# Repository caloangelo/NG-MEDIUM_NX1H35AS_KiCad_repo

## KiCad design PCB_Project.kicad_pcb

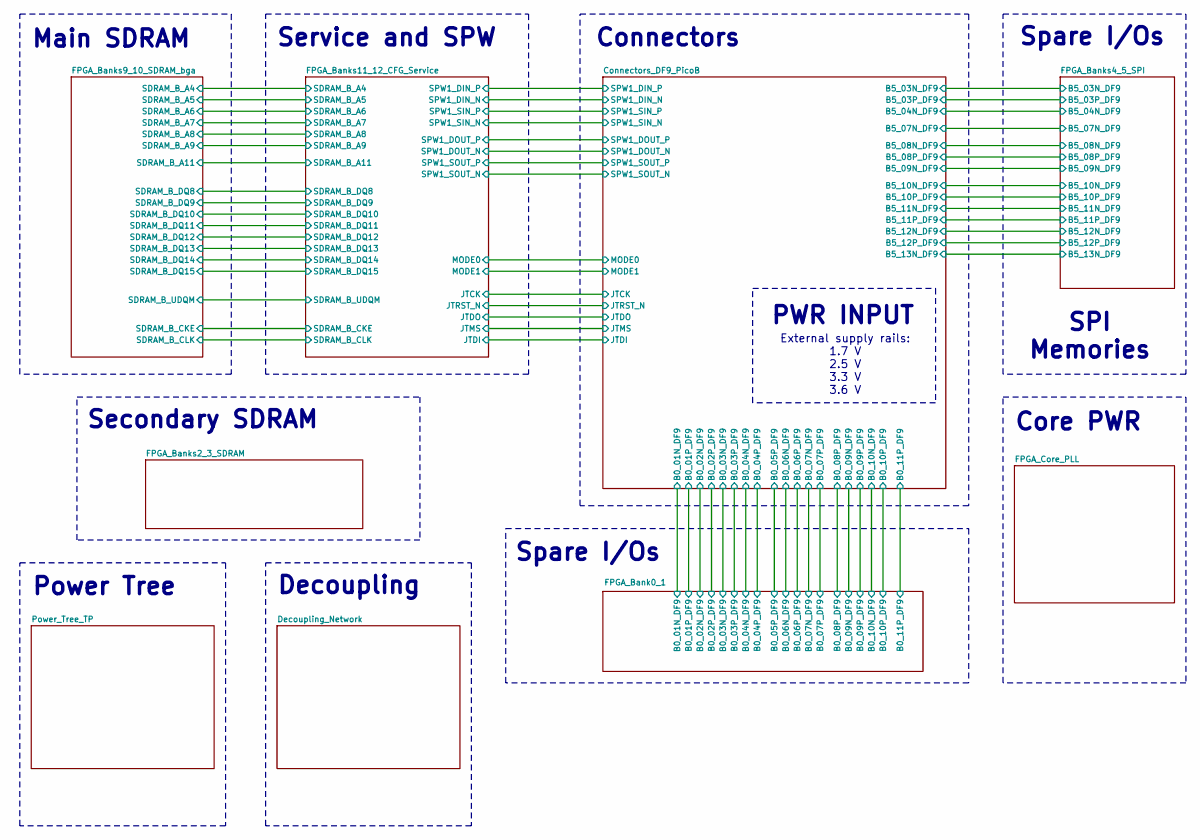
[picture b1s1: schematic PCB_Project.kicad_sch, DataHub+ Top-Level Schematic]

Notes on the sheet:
Spare I/Os
SPI Memories
Secondary SDRAM
Power Tree
Main SDRAM
Service and SPW
PWR INPUT
Decoupling
External supply rails: 1.7 V 2.5 V 3.3 V 3.6 V
Core PWR
Connectors

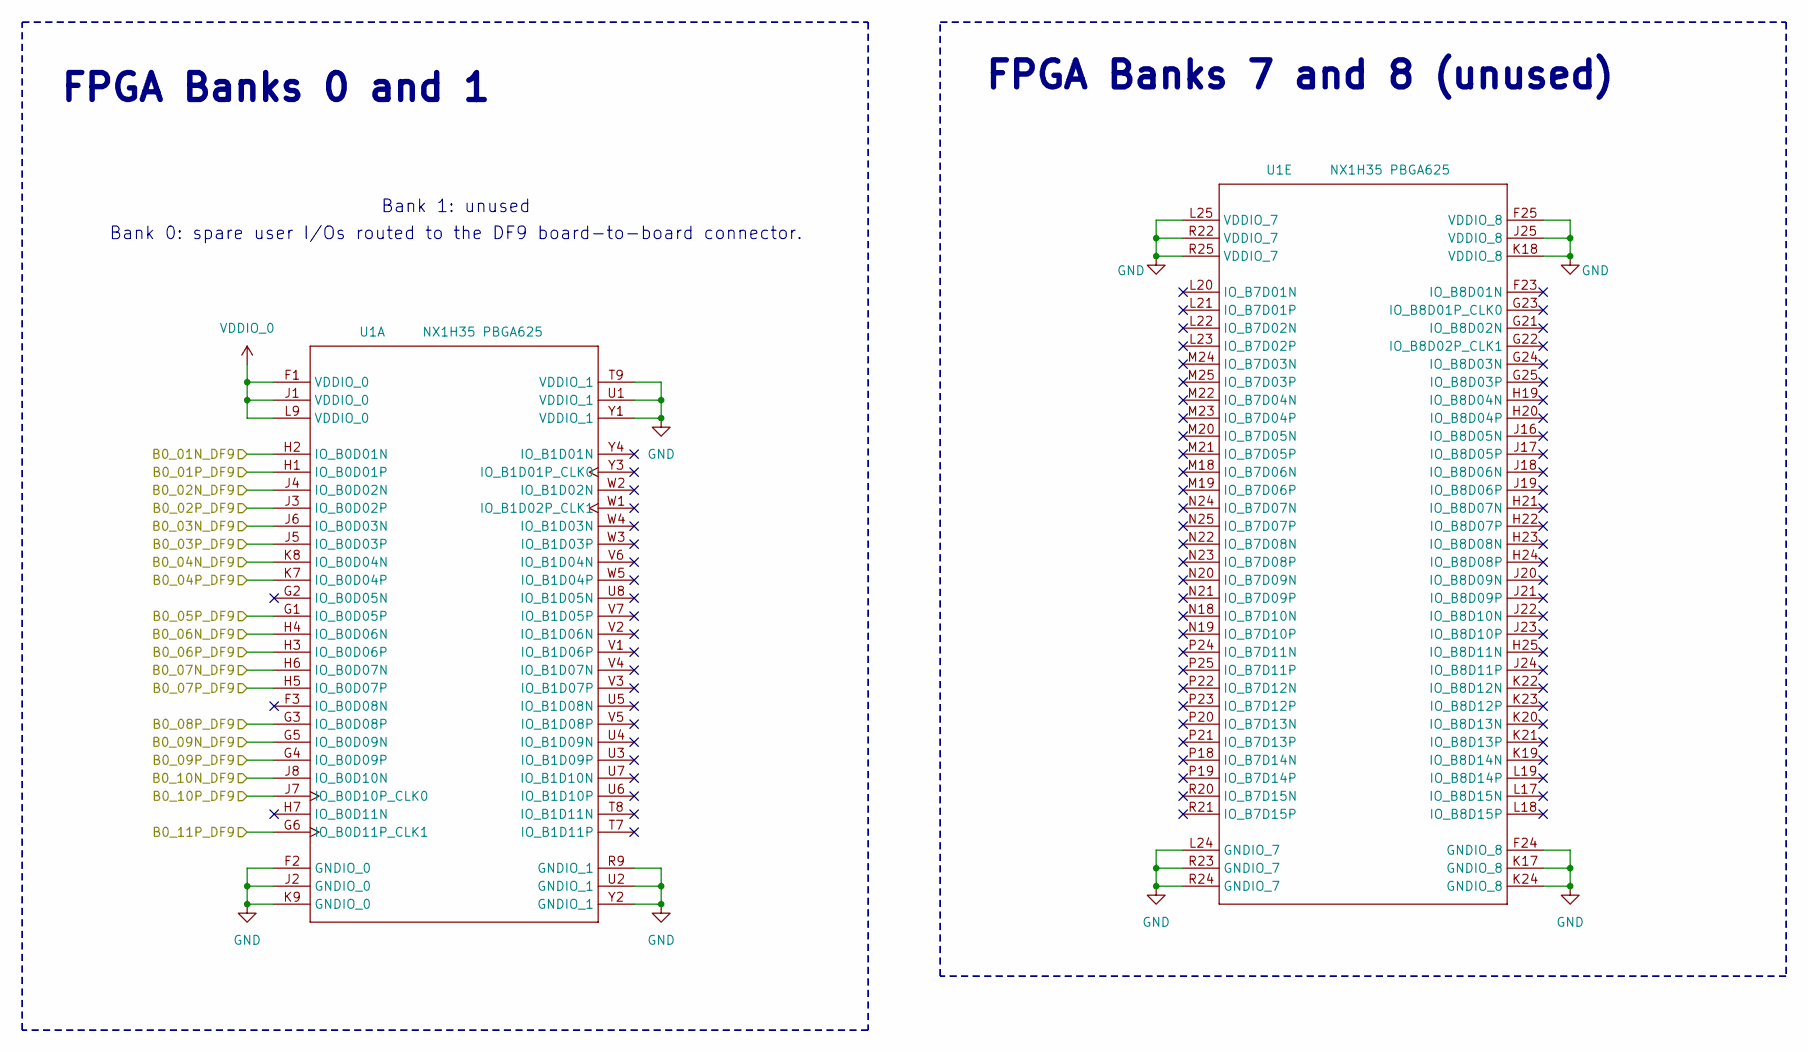
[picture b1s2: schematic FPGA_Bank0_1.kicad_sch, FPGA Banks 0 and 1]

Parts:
U1: NX1H35 PBGA625; NX1H35S_CLGA625

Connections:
/Connectors_DF9_PicoB/B0_01N_DF9: U1.H2 (IO_B0D01N); also elsewhere on the board
/Connectors_DF9_PicoB/B0_01P_DF9: U1.H1 (IO_B0D01P); also elsewhere on the board
/Connectors_DF9_PicoB/B0_02N_DF9: U1.J4 (IO_B0D02N); also elsewhere on the board
/Connectors_DF9_PicoB/B0_02P_DF9: U1.J3 (IO_B0D02P); also elsewhere on the board
/Connectors_DF9_PicoB/B0_03N_DF9: U1.J6 (IO_B0D03N); also elsewhere on the board
/Connectors_DF9_PicoB/B0_03P_DF9: U1.J5 (IO_B0D03P); also elsewhere on the board
/Connectors_DF9_PicoB/B0_04N_DF9: U1.K8 (IO_B0D04N); also elsewhere on the board
/Connectors_DF9_PicoB/B0_04P_DF9: U1.K7 (IO_B0D04P); also elsewhere on the board
/Connectors_DF9_PicoB/B0_05P_DF9: U1.G1 (IO_B0D05P); also elsewhere on the board
/Connectors_DF9_PicoB/B0_06N_DF9: U1.H4 (IO_B0D06N); also elsewhere on the board
/Connectors_DF9_PicoB/B0_06P_DF9: U1.H3 (IO_B0D06P); also elsewhere on the board
/Connectors_DF9_PicoB/B0_07N_DF9: U1.H6 (IO_B0D07N); also elsewhere on the board
/Connectors_DF9_PicoB/B0_07P_DF9: U1.H5 (IO_B0D07P); also elsewhere on the board
/Connectors_DF9_PicoB/B0_08P_DF9: U1.G3 (IO_B0D08P); also elsewhere on the board
/Connectors_DF9_PicoB/B0_09N_DF9: U1.G5 (IO_B0D09N); also elsewhere on the board
/Connectors_DF9_PicoB/B0_09P_DF9: U1.G4 (IO_B0D09P); also elsewhere on the board
/Connectors_DF9_PicoB/B0_10N_DF9: U1.J8 (IO_B0D10N); also elsewhere on the board
/Connectors_DF9_PicoB/B0_10P_DF9: U1.J7 (IO_B0D10P_CLK0); also elsewhere on the board
/Connectors_DF9_PicoB/B0_11P_DF9: U1.G6 (IO_B0D11P_CLK1); also elsewhere on the board
GND: U1.F2 (GNDIO_0), U1.F24 (GNDIO_8), U1.F25 (VDDIO_8), U1.J2 (GNDIO_0), U1.J25 (VDDIO_8), U1.K9 (GNDIO_0), U1.K17 (GNDIO_8), U1.K18 (VDDIO_8), U1.K24 (GNDIO_8), U1.L24 (GNDIO_7), U1.L25 (VDDIO_7), U1.R9 (GNDIO_1), U1.R22 (VDDIO_7), U1.R23 (GNDIO_7), U1.R24 (GNDIO_7), U1.R25 (VDDIO_7), U1.T9 (VDDIO_1), U1.U1 (VDDIO_1), U1.U2 (GNDIO_1), U1.Y1 (VDDIO_1), U1.Y2 (GNDIO_1); also elsewhere on the board
VDD3V3: U1.F1 (VDDIO_0), U1.J1 (VDDIO_0), U1.L9 (VDDIO_0); also elsewhere on the board

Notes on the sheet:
Bank 0: spare user I/Os routed to the DF9 board-to-board connector.
FPGA Banks 0 and 1
FPGA Banks 7 and 8 (unused)
Bank 1: unused

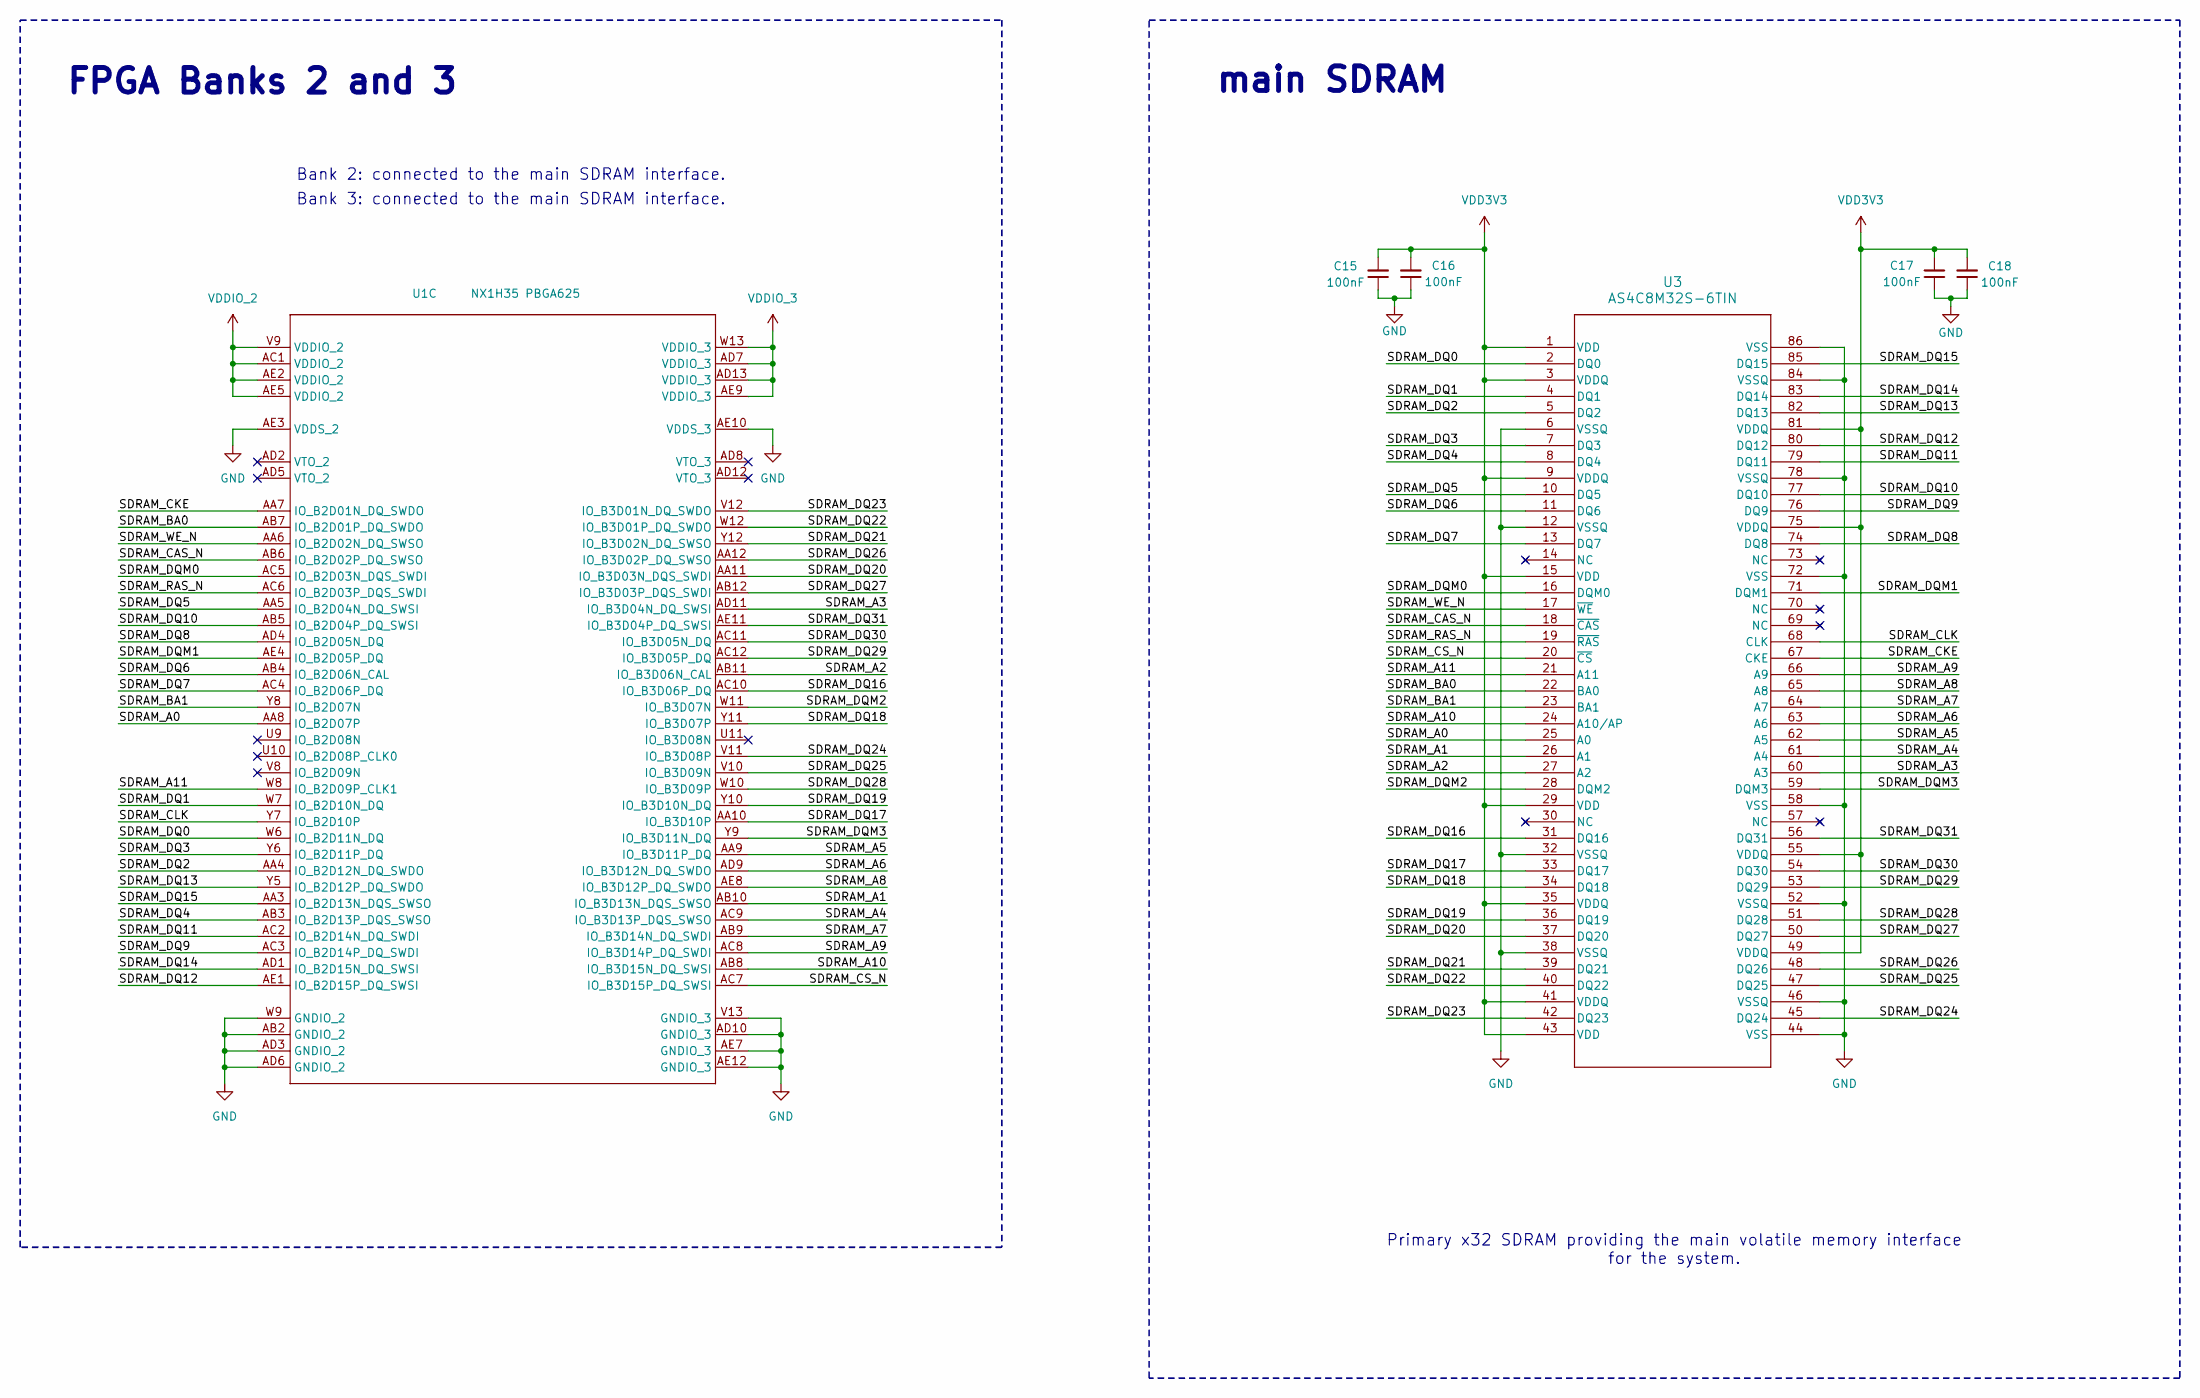
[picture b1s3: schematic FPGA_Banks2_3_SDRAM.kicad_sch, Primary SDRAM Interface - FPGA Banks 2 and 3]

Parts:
C15, C16, C17, C18: 100nF; C_0402_1005Metric_Pad0.74x0.62mm_HandSolder
U1: NX1H35 PBGA625; NX1H35S_CLGA625
U3: AS4C8M32S-6TIN; AS4C8M32S_TSOP-II-86_ALL

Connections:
/FPGA_Banks2_3_SDRAM/SDRAM_A0: U1.AA8 (IO_B2D07P), U3.25 (A0)
/FPGA_Banks2_3_SDRAM/SDRAM_A1: U1.AB10 (IO_B3D13N_DQS_SWSO), U3.26 (A1)
/FPGA_Banks2_3_SDRAM/SDRAM_A2: U1.AB11 (IO_B3D06N_CAL), U3.27 (A2)
/FPGA_Banks2_3_SDRAM/SDRAM_A3: U1.AD11 (IO_B3D04N_DQ_SWSI), U3.60 (A3)
/FPGA_Banks2_3_SDRAM/SDRAM_A4: U1.AC9 (IO_B3D13P_DQS_SWSO), U3.61 (A4)
/FPGA_Banks2_3_SDRAM/SDRAM_A5: U1.AA9 (IO_B3D11P_DQ), U3.62 (A5)
/FPGA_Banks2_3_SDRAM/SDRAM_A6: U1.AD9 (IO_B3D12N_DQ_SWDO), U3.63 (A6)
/FPGA_Banks2_3_SDRAM/SDRAM_A7: U1.AB9 (IO_B3D14N_DQ_SWDI), U3.64 (A7)
/FPGA_Banks2_3_SDRAM/SDRAM_A8: U1.AE8 (IO_B3D12P_DQ_SWDO), U3.65 (A8)
/FPGA_Banks2_3_SDRAM/SDRAM_A9: U1.AC8 (IO_B3D14P_DQ_SWDI), U3.66 (A9)
/FPGA_Banks2_3_SDRAM/SDRAM_A10: U1.AB8 (IO_B3D15N_DQ_SWSI), U3.24 (A10/AP)
/FPGA_Banks2_3_SDRAM/SDRAM_A11: U1.W8 (IO_B2D09P_CLK1), U3.21 (A11)
/FPGA_Banks2_3_SDRAM/SDRAM_BA0: U1.AB7 (IO_B2D01P_DQ_SWDO), U3.22 (BA0)
/FPGA_Banks2_3_SDRAM/SDRAM_BA1: U1.Y8 (IO_B2D07N), U3.23 (BA1)
/FPGA_Banks2_3_SDRAM/SDRAM_CAS_N: U1.AB6 (IO_B2D02P_DQ_SWSO), U3.18 (~CAS)
/FPGA_Banks2_3_SDRAM/SDRAM_CKE: U1.AA7 (IO_B2D01N_DQ_SWDO), U3.67 (CKE)
/FPGA_Banks2_3_SDRAM/SDRAM_CLK: U1.Y7 (IO_B2D10P), U3.68 (CLK)
/FPGA_Banks2_3_SDRAM/SDRAM_CS_N: U1.AC7 (IO_B3D15P_DQ_SWSI), U3.20 (~CS)
/FPGA_Banks2_3_SDRAM/SDRAM_DQ0: U1.W6 (IO_B2D11N_DQ), U3.2 (DQ0)
/FPGA_Banks2_3_SDRAM/SDRAM_DQ1: U1.W7 (IO_B2D10N_DQ), U3.4 (DQ1)
/FPGA_Banks2_3_SDRAM/SDRAM_DQ2: U1.AA4 (IO_B2D12N_DQ_SWDO), U3.5 (DQ2)
/FPGA_Banks2_3_SDRAM/SDRAM_DQ3: U1.Y6 (IO_B2D11P_DQ), U3.7 (DQ3)
/FPGA_Banks2_3_SDRAM/SDRAM_DQ4: U1.AB3 (IO_B2D13P_DQS_SWSO), U3.8 (DQ4)
/FPGA_Banks2_3_SDRAM/SDRAM_DQ5: U1.AA5 (IO_B2D04N_DQ_SWSI), U3.10 (DQ5)
/FPGA_Banks2_3_SDRAM/SDRAM_DQ6: U1.AB4 (IO_B2D06N_CAL), U3.11 (DQ6)
/FPGA_Banks2_3_SDRAM/SDRAM_DQ7: U1.AC4 (IO_B2D06P_DQ), U3.13 (DQ7)
/FPGA_Banks2_3_SDRAM/SDRAM_DQ8: U1.AD4 (IO_B2D05N_DQ), U3.74 (DQ8)
/FPGA_Banks2_3_SDRAM/SDRAM_DQ9: U1.AC3 (IO_B2D14P_DQ_SWDI), U3.76 (DQ9)
/FPGA_Banks2_3_SDRAM/SDRAM_DQ10: U1.AB5 (IO_B2D04P_DQ_SWSI), U3.77 (DQ10)
/FPGA_Banks2_3_SDRAM/SDRAM_DQ11: U1.AC2 (IO_B2D14N_DQ_SWDI), U3.79 (DQ11)
/FPGA_Banks2_3_SDRAM/SDRAM_DQ12: U1.AE1 (IO_B2D15P_DQ_SWSI), U3.80 (DQ12)
/FPGA_Banks2_3_SDRAM/SDRAM_DQ13: U1.Y5 (IO_B2D12P_DQ_SWDO), U3.82 (DQ13)
/FPGA_Banks2_3_SDRAM/SDRAM_DQ14: U1.AD1 (IO_B2D15N_DQ_SWSI), U3.83 (DQ14)
/FPGA_Banks2_3_SDRAM/SDRAM_DQ15: U1.AA3 (IO_B2D13N_DQS_SWSO), U3.85 (DQ15)
/FPGA_Banks2_3_SDRAM/SDRAM_DQ16: U1.AC10 (IO_B3D06P_DQ), U3.31 (DQ16)
/FPGA_Banks2_3_SDRAM/SDRAM_DQ17: U1.AA10 (IO_B3D10P), U3.33 (DQ17)
/FPGA_Banks2_3_SDRAM/SDRAM_DQ18: U1.Y11 (IO_B3D07P), U3.34 (DQ18)
/FPGA_Banks2_3_SDRAM/SDRAM_DQ19: U1.Y10 (IO_B3D10N_DQ), U3.36 (DQ19)
/FPGA_Banks2_3_SDRAM/SDRAM_DQ20: U1.AA11 (IO_B3D03N_DQS_SWDI), U3.37 (DQ20)
/FPGA_Banks2_3_SDRAM/SDRAM_DQ21: U1.Y12 (IO_B3D02N_DQ_SWSO), U3.39 (DQ21)
/FPGA_Banks2_3_SDRAM/SDRAM_DQ22: U1.W12 (IO_B3D01P_DQ_SWDO), U3.40 (DQ22)
/FPGA_Banks2_3_SDRAM/SDRAM_DQ23: U1.V12 (IO_B3D01N_DQ_SWDO), U3.42 (DQ23)
/FPGA_Banks2_3_SDRAM/SDRAM_DQ24: U1.V11 (IO_B3D08P), U3.45 (DQ24)
/FPGA_Banks2_3_SDRAM/SDRAM_DQ25: U1.V10 (IO_B3D09N), U3.47 (DQ25)
/FPGA_Banks2_3_SDRAM/SDRAM_DQ26: U1.AA12 (IO_B3D02P_DQ_SWSO), U3.48 (DQ26)
/FPGA_Banks2_3_SDRAM/SDRAM_DQ27: U1.AB12 (IO_B3D03P_DQS_SWDI), U3.50 (DQ27)
/FPGA_Banks2_3_SDRAM/SDRAM_DQ28: U1.W10 (IO_B3D09P), U3.51 (DQ28)
/FPGA_Banks2_3_SDRAM/SDRAM_DQ29: U1.AC12 (IO_B3D05P_DQ), U3.53 (DQ29)
/FPGA_Banks2_3_SDRAM/SDRAM_DQ30: U1.AC11 (IO_B3D05N_DQ), U3.54 (DQ30)
/FPGA_Banks2_3_SDRAM/SDRAM_DQ31: U1.AE11 (IO_B3D04P_DQ_SWSI), U3.56 (DQ31)
/FPGA_Banks2_3_SDRAM/SDRAM_DQM0: U1.AC5 (IO_B2D03N_DQS_SWDI), U3.16 (DQM0)
/FPGA_Banks2_3_SDRAM/SDRAM_DQM1: U1.AE4 (IO_B2D05P_DQ), U3.71 (DQM1)
/FPGA_Banks2_3_SDRAM/SDRAM_DQM2: U1.W11 (IO_B3D07N), U3.28 (DQM2)
/FPGA_Banks2_3_SDRAM/SDRAM_DQM3: U1.Y9 (IO_B3D11N_DQ), U3.59 (DQM3)
/FPGA_Banks2_3_SDRAM/SDRAM_RAS_N: U1.AC6 (IO_B2D03P_DQS_SWDI), U3.19 (~RAS)
/FPGA_Banks2_3_SDRAM/SDRAM_WE_N: U1.AA6 (IO_B2D02N_DQ_SWSO), U3.17 (~WE)
GND: C15.1, C16.1, C17.1, C18.1, U1.AB2 (GNDIO_2), U1.AD3 (GNDIO_2), U1.AD6 (GNDIO_2), U1.AD10 (GNDIO_3), U1.AE3 (VDDS_2), U1.AE7 (GNDIO_3), U1.AE10 (VDDS_3), U1.AE12 (GNDIO_3), U1.V13 (GNDIO_3), U1.W9 (GNDIO_2), U3.6 (VSSQ), U3.12 (VSSQ), U3.32 (VSSQ), U3.38 (VSSQ), U3.44 (VSS), U3.46 (VSSQ), U3.52 (VSSQ), U3.58 (VSS), U3.72 (VSS), U3.78 (VSSQ), U3.84 (VSSQ), U3.86 (VSS); also elsewhere on the board
VDD3V3: C15.2, C16.2, C17.2, C18.2, U1.AC1 (VDDIO_2), U1.AD7 (VDDIO_3), U1.AD13 (VDDIO_3), U1.AE2 (VDDIO_2), U1.AE5 (VDDIO_2), U1.AE9 (VDDIO_3), U1.V9 (VDDIO_2), U1.W13 (VDDIO_3), U3.1 (VDD), U3.3 (VDDQ), U3.9 (VDDQ), U3.15 (VDD), U3.29 (VDD), U3.35 (VDDQ), U3.41 (VDDQ), U3.43 (VDD), U3.49 (VDDQ), U3.55 (VDDQ), U3.75 (VDDQ), U3.81 (VDDQ); also elsewhere on the board

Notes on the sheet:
Bank 3: connected to the main SDRAM interface.
main SDRAM
FPGA Banks 2 and 3
Primary x32 SDRAM providing the main volatile memory interface for the system.
Bank 2: connected to the main SDRAM interface.

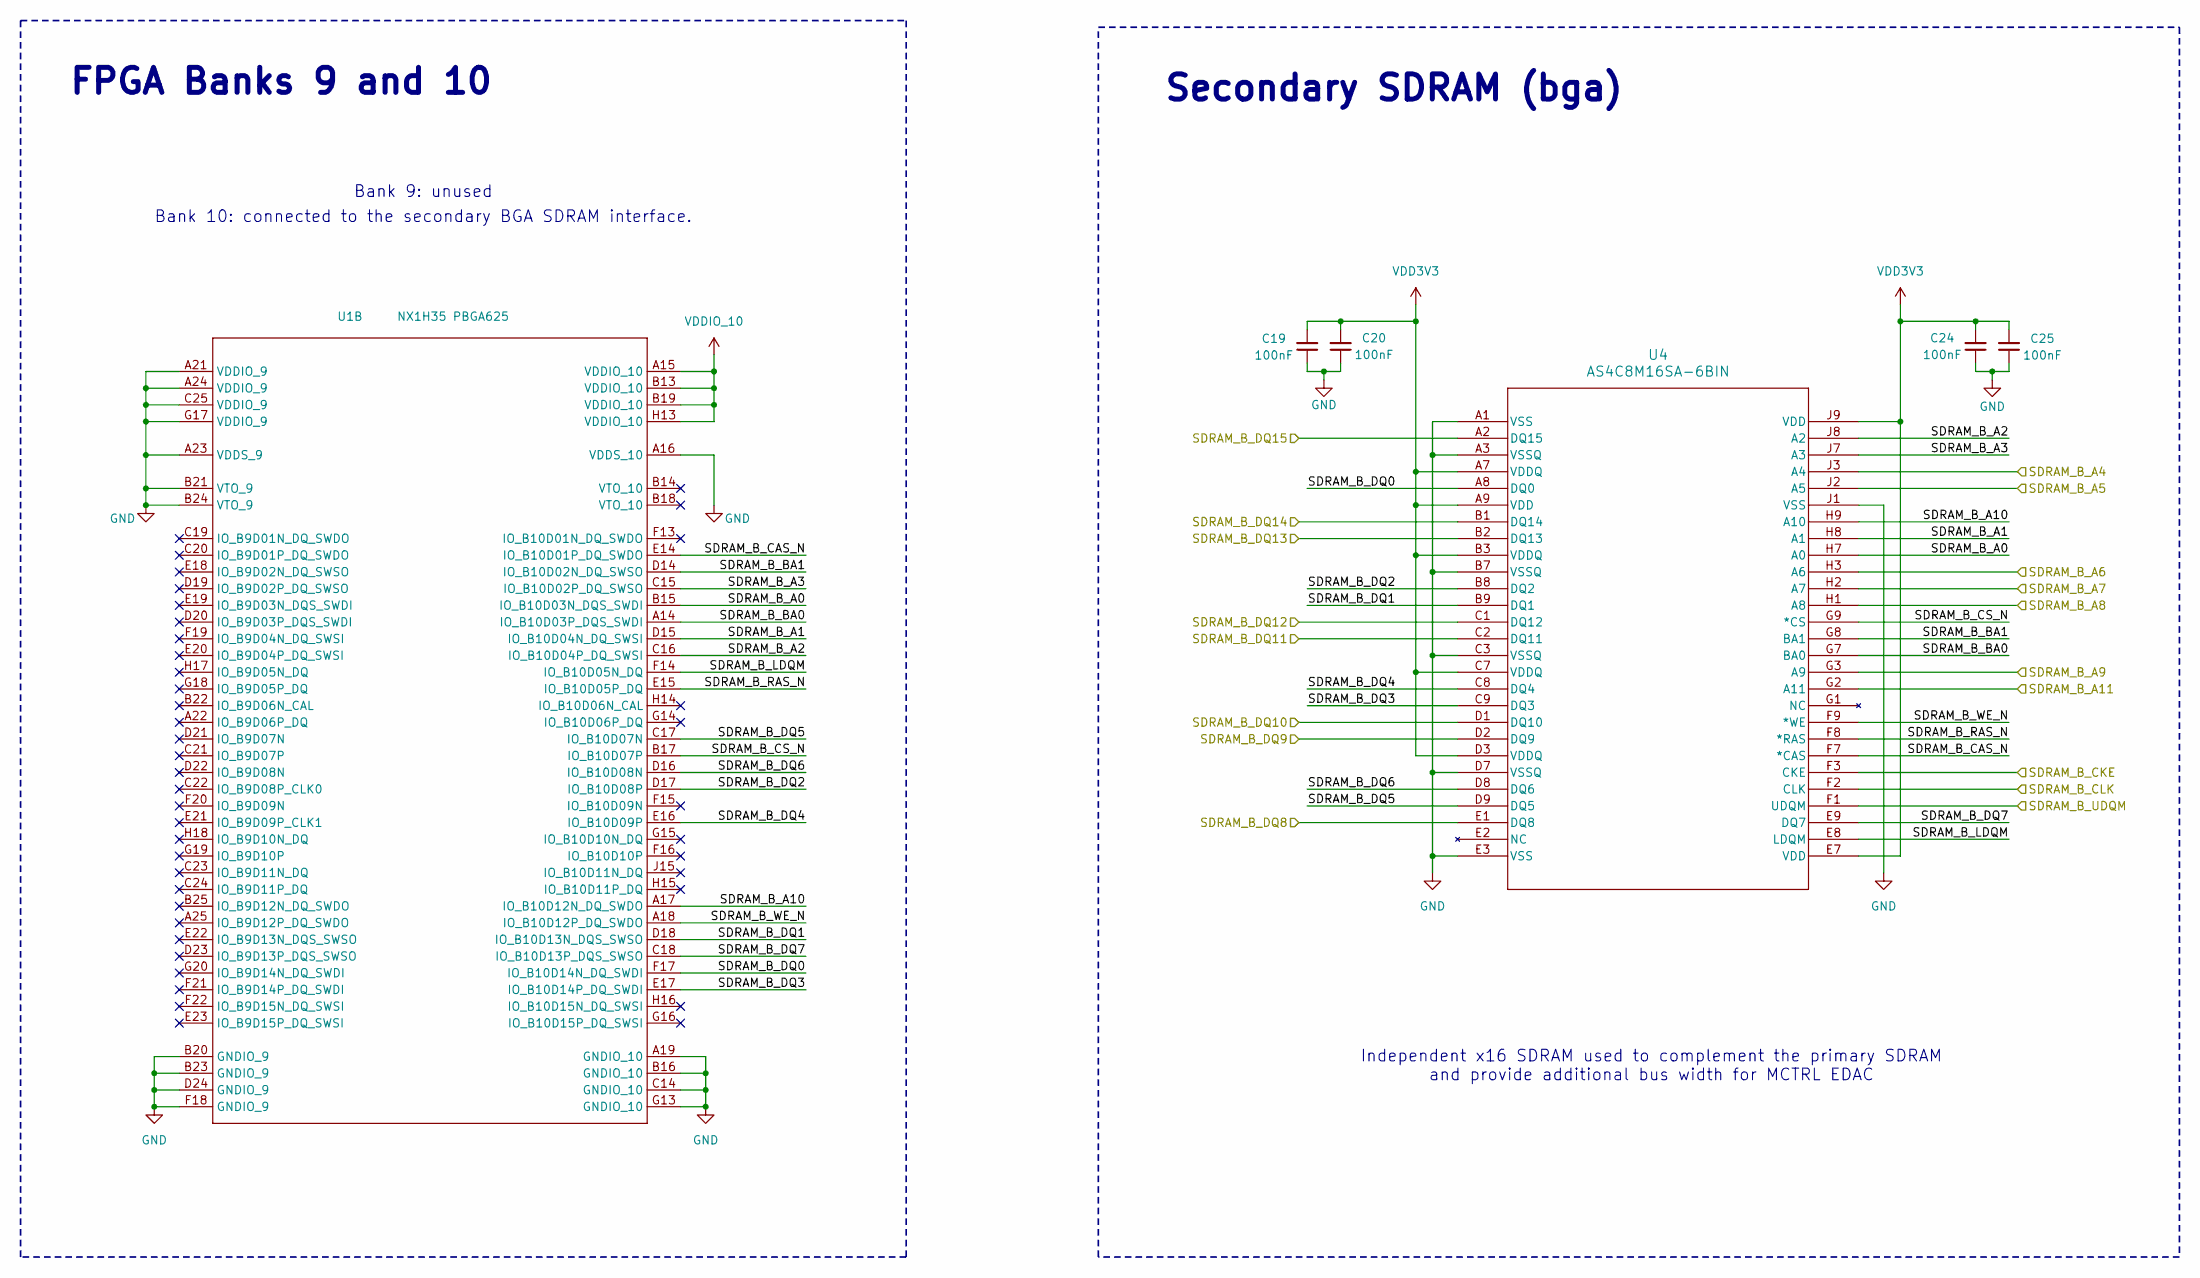
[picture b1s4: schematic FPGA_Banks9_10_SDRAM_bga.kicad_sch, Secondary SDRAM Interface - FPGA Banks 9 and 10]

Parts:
C19, C20, C24, C25: 100nF; C_0402_1005Metric_Pad0.74x0.62mm_HandSolder
U1: NX1H35 PBGA625; NX1H35S_CLGA625
U4: AS4C8M16SA-6BIN; sdram2_bga_TFBGA-54_8X8_ALL

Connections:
/FPGA_Banks9_10_SDRAM_bga/SDRAM_B_A0: U1.B15 (IO_B10D03N_DQS_SWDI), U4.H7 (A0)
/FPGA_Banks9_10_SDRAM_bga/SDRAM_B_A1: U1.D15 (IO_B10D04N_DQ_SWSI), U4.H8 (A1)
/FPGA_Banks9_10_SDRAM_bga/SDRAM_B_A2: U1.C16 (IO_B10D04P_DQ_SWSI), U4.J8 (A2)
/FPGA_Banks9_10_SDRAM_bga/SDRAM_B_A3: U1.C15 (IO_B10D02P_DQ_SWSO), U4.J7 (A3)
/FPGA_Banks9_10_SDRAM_bga/SDRAM_B_A10: U1.A17 (IO_B10D12N_DQ_SWDO), U4.H9 (A10)
/FPGA_Banks9_10_SDRAM_bga/SDRAM_B_BA0: U1.A14 (IO_B10D03P_DQS_SWDI), U4.G7 (BA0)
/FPGA_Banks9_10_SDRAM_bga/SDRAM_B_BA1: U1.D14 (IO_B10D02N_DQ_SWSO), U4.G8 (BA1)
/FPGA_Banks9_10_SDRAM_bga/SDRAM_B_CAS_N: U1.E14 (IO_B10D01P_DQ_SWDO), U4.F7 (*CAS)
/FPGA_Banks9_10_SDRAM_bga/SDRAM_B_CS_N: U1.B17 (IO_B10D07P), U4.G9 (*CS)
/FPGA_Banks9_10_SDRAM_bga/SDRAM_B_DQ0: U1.F17 (IO_B10D14N_DQ_SWDI), U4.A8 (DQ0)
/FPGA_Banks9_10_SDRAM_bga/SDRAM_B_DQ1: U1.D18 (IO_B10D13N_DQS_SWSO), U4.B9 (DQ1)
/FPGA_Banks9_10_SDRAM_bga/SDRAM_B_DQ2: U1.D17 (IO_B10D08P), U4.B8 (DQ2)
/FPGA_Banks9_10_SDRAM_bga/SDRAM_B_DQ3: U1.E17 (IO_B10D14P_DQ_SWDI), U4.C9 (DQ3)
/FPGA_Banks9_10_SDRAM_bga/SDRAM_B_DQ4: U1.E16 (IO_B10D09P), U4.C8 (DQ4)
/FPGA_Banks9_10_SDRAM_bga/SDRAM_B_DQ5: U1.C17 (IO_B10D07N), U4.D9 (DQ5)
/FPGA_Banks9_10_SDRAM_bga/SDRAM_B_DQ6: U1.D16 (IO_B10D08N), U4.D8 (DQ6)
/FPGA_Banks9_10_SDRAM_bga/SDRAM_B_DQ7: U1.C18 (IO_B10D13P_DQS_SWSO), U4.E9 (DQ7)
/FPGA_Banks9_10_SDRAM_bga/SDRAM_B_LDQM: U1.F14 (IO_B10D05N_DQ), U4.E8 (LDQM)
/FPGA_Banks9_10_SDRAM_bga/SDRAM_B_RAS_N: U1.E15 (IO_B10D05P_DQ), U4.F8 (*RAS)
/FPGA_Banks9_10_SDRAM_bga/SDRAM_B_WE_N: U1.A18 (IO_B10D12P_DQ_SWDO), U4.F9 (*WE)
/FPGA_Banks11_12_CFG_Service/SDRAM_B_A4: U4.J3 (A4); also elsewhere on the board
/FPGA_Banks11_12_CFG_Service/SDRAM_B_A5: U4.J2 (A5); also elsewhere on the board
/FPGA_Banks11_12_CFG_Service/SDRAM_B_A6: U4.H3 (A6); also elsewhere on the board
/FPGA_Banks11_12_CFG_Service/SDRAM_B_A7: U4.H2 (A7); also elsewhere on the board
/FPGA_Banks11_12_CFG_Service/SDRAM_B_A8: U4.H1 (A8); also elsewhere on the board
/FPGA_Banks11_12_CFG_Service/SDRAM_B_A9: U4.G3 (A9); also elsewhere on the board
/FPGA_Banks11_12_CFG_Service/SDRAM_B_A11: U4.G2 (A11); also elsewhere on the board
/FPGA_Banks11_12_CFG_Service/SDRAM_B_CKE: U4.F3 (CKE); also elsewhere on the board
/FPGA_Banks11_12_CFG_Service/SDRAM_B_CLK: U4.F2 (CLK); also elsewhere on the board
/FPGA_Banks11_12_CFG_Service/SDRAM_B_DQ8: U4.E1 (DQ8); also elsewhere on the board
/FPGA_Banks11_12_CFG_Service/SDRAM_B_DQ9: U4.D2 (DQ9); also elsewhere on the board
/FPGA_Banks11_12_CFG_Service/SDRAM_B_DQ10: U4.D1 (DQ10); also elsewhere on the board
/FPGA_Banks11_12_CFG_Service/SDRAM_B_DQ11: U4.C2 (DQ11); also elsewhere on the board
/FPGA_Banks11_12_CFG_Service/SDRAM_B_DQ12: U4.C1 (DQ12); also elsewhere on the board
/FPGA_Banks11_12_CFG_Service/SDRAM_B_DQ13: U4.B2 (DQ13); also elsewhere on the board
/FPGA_Banks11_12_CFG_Service/SDRAM_B_DQ14: U4.B1 (DQ14); also elsewhere on the board
/FPGA_Banks11_12_CFG_Service/SDRAM_B_DQ15: U4.A2 (DQ15); also elsewhere on the board
/FPGA_Banks11_12_CFG_Service/SDRAM_B_UDQM: U4.F1 (UDQM); also elsewhere on the board
GND: C19.1, C20.1, C24.1, C25.1, U1.A16 (VDDS_10), U1.A19 (GNDIO_10), U1.A21 (VDDIO_9), U1.A23 (VDDS_9), U1.A24 (VDDIO_9), U1.B16 (GNDIO_10), U1.B20 (GNDIO_9), U1.B21 (VTO_9), U1.B23 (GNDIO_9), U1.B24 (VTO_9), U1.C14 (GNDIO_10), U1.C25 (VDDIO_9), U1.D24 (GNDIO_9), U1.F18 (GNDIO_9), U1.G13 (GNDIO_10), U1.G17 (VDDIO_9), U4.A1 (VSS), U4.A3 (VSSQ), U4.B7 (VSSQ), U4.C3 (VSSQ), U4.D7 (VSSQ), U4.E3 (VSS), U4.J1 (VSS); also elsewhere on the board
VDD3V3: C19.2, C20.2, C24.2, C25.2, U1.A15 (VDDIO_10), U1.B13 (VDDIO_10), U1.B19 (VDDIO_10), U1.H13 (VDDIO_10), U4.A7 (VDDQ), U4.A9 (VDD), U4.B3 (VDDQ), U4.C7 (VDDQ), U4.D3 (VDDQ), U4.E7 (VDD), U4.J9 (VDD); also elsewhere on the board

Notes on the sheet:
Bank 9: unused
FPGA Banks 9 and 10
Secondary SDRAM (bga)
Independent x16 SDRAM used to complement the primary SDRAM and provide additional bus width for MCTRL EDAC
Bank 10: connected to the secondary BGA SDRAM interface.

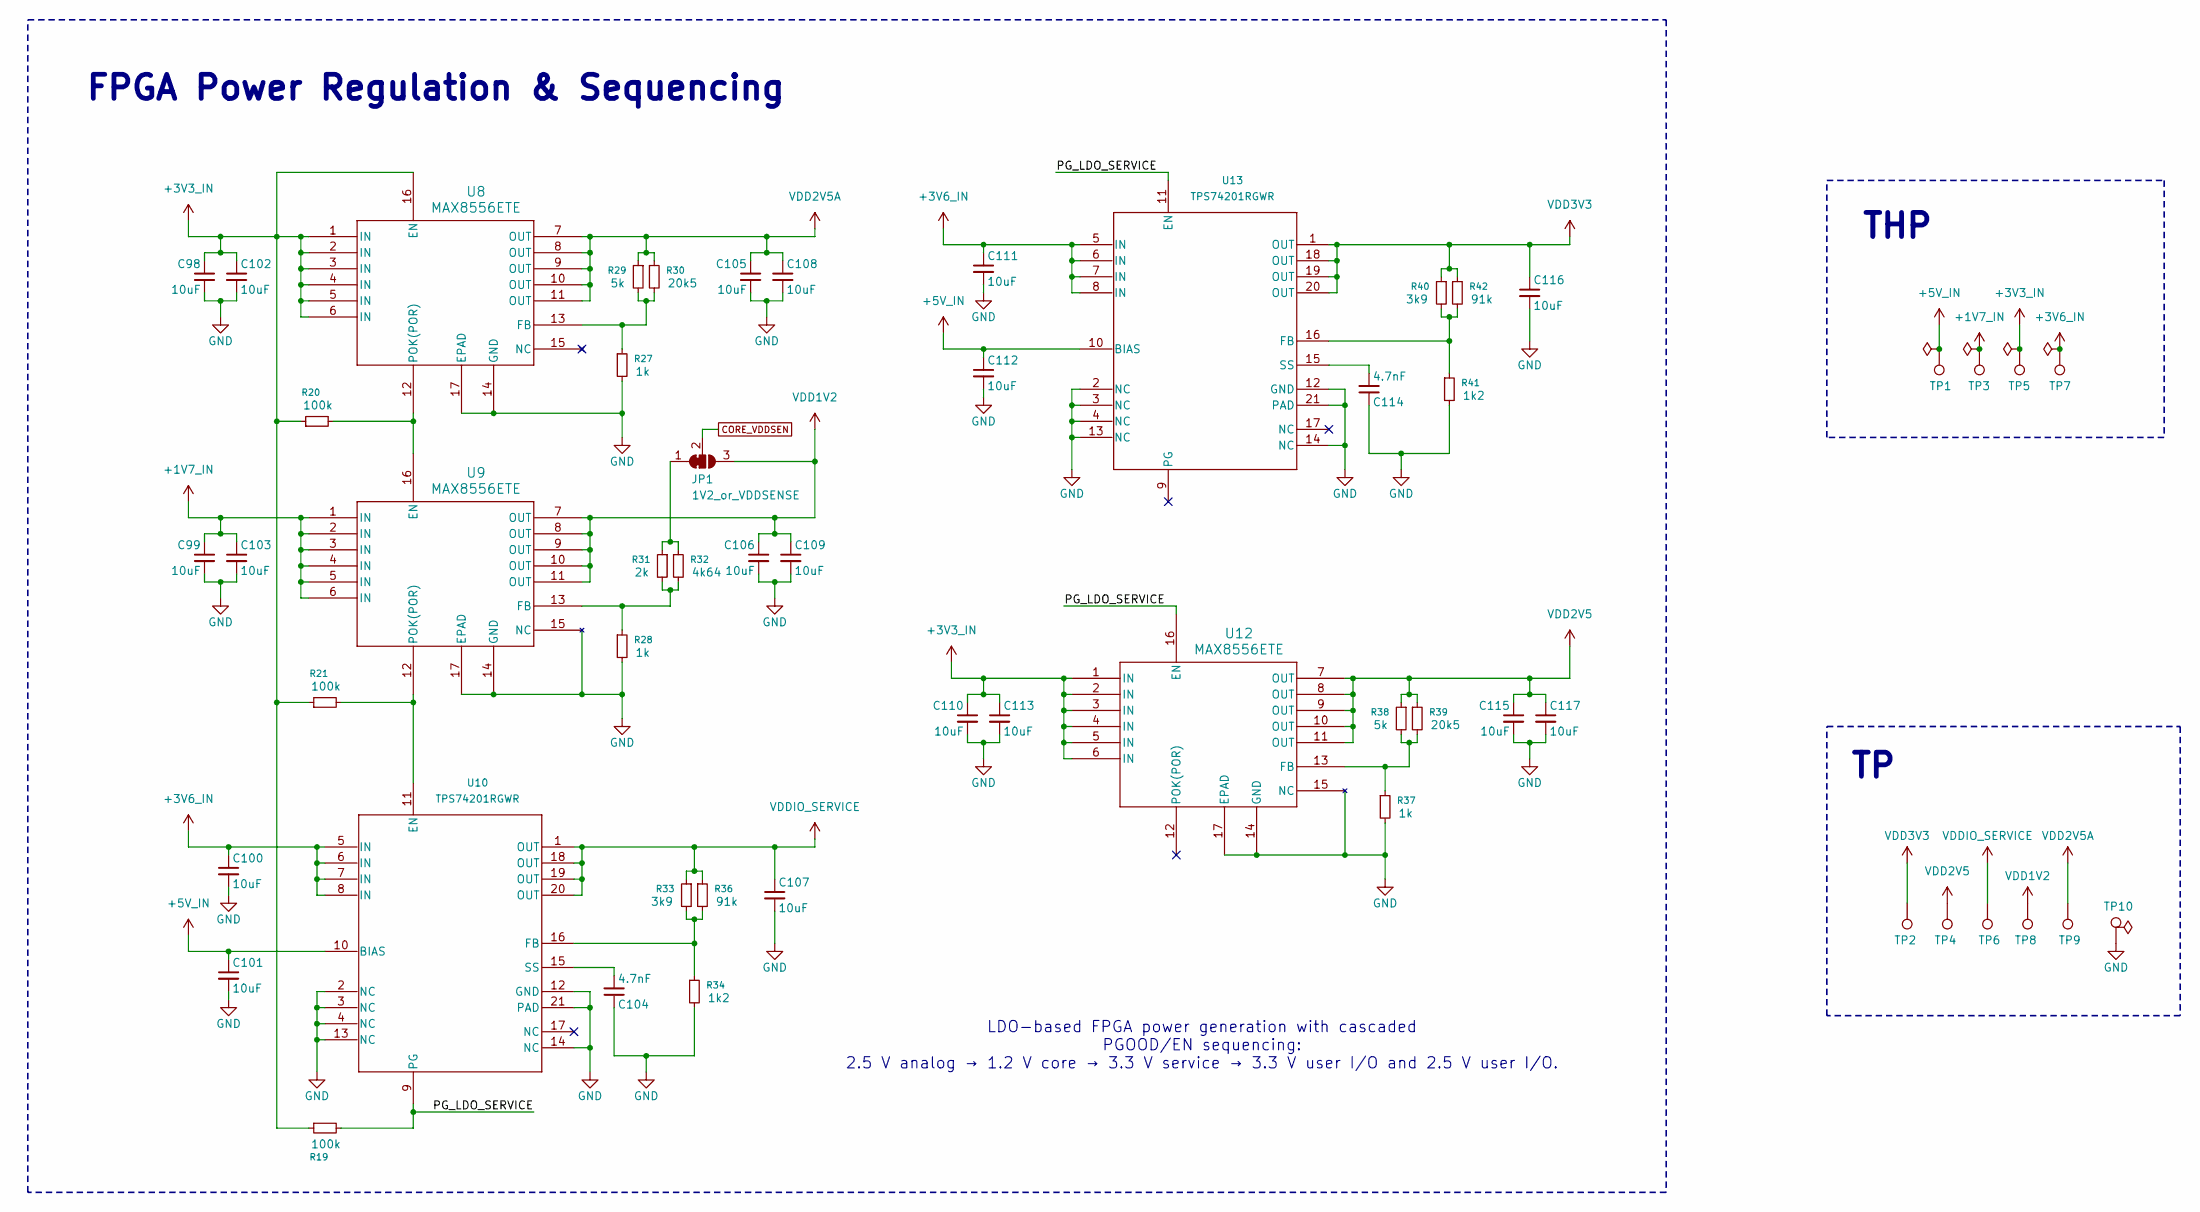
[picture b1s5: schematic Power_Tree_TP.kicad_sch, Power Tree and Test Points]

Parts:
C98, C99, C100, C101, C102, C103, C105, C106, C107, C108, C109, C110, C111, C112, C113, C115, C116, C117: 10uF; C_0603_1608Metric_Pad1.08x0.95mm_HandSolder
C104, C114: 4.7nF; C_0402_1005Metric_Pad0.74x0.62mm_HandSolder
JP1: 1V2_or_VDDSENSE; SolderJumper-3_P1.3mm_Bridged2Bar12_RoundedPad1.0x1.5mm
R19, R20, R21: 100k; R_0402_1005Metric_Pad0.72x0.64mm_HandSolder
R27, R28, R37: 1k; R_0402_1005Metric_Pad0.72x0.64mm_HandSolder
R29, R38: 5k; R_0402_1005Metric_Pad0.72x0.64mm_HandSolder
R30, R39: 20k5; R_0402_1005Metric_Pad0.72x0.64mm_HandSolder
R31: 2k; R_0402_1005Metric_Pad0.72x0.64mm_HandSolder
R32: 4k64; R_0402_1005Metric_Pad0.72x0.64mm_HandSolder
R33, R40: 3k9; R_0402_1005Metric_Pad0.72x0.64mm_HandSolder
R34, R41: 1k2; R_0402_1005Metric_Pad0.72x0.64mm_HandSolder
R36, R42: 91k; R_0402_1005Metric_Pad0.72x0.64mm_HandSolder
TP1: 5V; PTH_pad_2x0.8
TP2, TP6: 3V3; Test_Point
TP3: 1V7; PTH_pad_2x0.8
TP4: 2V5; Test_Point
TP5: 3V3; PTH_pad_2x0.8
TP7: 3V6; PTH_pad_2x0.8
TP8: 1V2; Test_Point
TP9: 2V5A; Test_Point
TP10: GND; Test_Point
U8, U9, U12: MAX8556ETE; MAX8556
U10, U13: TPS74201RGWR; TPS74201

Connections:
+1V7_IN: C99.1, C103.1, TP3.1, U9.1 (IN), U9.2 (IN), U9.3 (IN), U9.4 (IN), U9.5 (IN), U9.6 (IN); also elsewhere on the board
+3V3_IN: C98.1, C102.1, C110.1, C113.1, R19.1, R20.1, R21.1, TP5.1, U8.1 (IN), U8.2 (IN), U8.3 (IN), U8.4 (IN), U8.5 (IN), U8.6 (IN), U8.16 (EN), U12.1 (IN), U12.2 (IN), U12.3 (IN), U12.4 (IN), U12.5 (IN), U12.6 (IN); also elsewhere on the board
+3V6_IN: C100.1, C111.1, TP7.1, U10.5 (IN), U10.6 (IN), U10.7 (IN), U10.8 (IN), U13.5 (IN), U13.6 (IN), U13.7 (IN), U13.8 (IN); also elsewhere on the board
+5V_IN: C101.1, C112.1, TP1.1, U10.10 (BIAS), U13.10 (BIAS); also elsewhere on the board
/Power_Tree_TP/PG_LDO_SERVICE: R19.2, U10.9 (PG), U12.16 (EN), U13.11 (EN)
CORE_VDDSEN: JP1.2 (C); also elsewhere on the board
GND: C98.2, C99.2, C100.2, C101.2, C102.2, C103.2, C104.1, C105.2, C106.2, C107.2, C108.2, C109.2, C110.2, C111.2, C112.2, C113.2, C114.1, C115.2, C116.2, C117.2, R27.2, R28.2, R34.2, R37.2, R41.2, TP10.1, U8.14 (GND), U8.17 (EPAD), U9.14 (GND), U9.15 (NC), U9.17 (EPAD), U10.2 (NC), U10.3 (NC), U10.4 (NC), U10.12 (GND), U10.13 (NC), U10.14 (NC), U10.21 (PAD), U12.14 (GND), U12.15 (NC), U12.17 (EPAD), U13.2 (NC), U13.3 (NC), U13.4 (NC), U13.12 (GND), U13.13 (NC), U13.14 (NC), U13.21 (PAD); also elsewhere on the board
unnamed: JP1.1 (A), R31.1, R32.1
unnamed: R27.1, R29.2, R30.2, U8.13 (FB)
unnamed: R20.2, U8.12 (POK(POR)), U9.16 (EN)
unnamed: R28.1, R31.2, R32.2, U9.13 (FB)
unnamed: R21.2, U9.12 (POK(POR)), U10.11 (EN)
unnamed: R33.2, R34.1, R36.2, U10.16 (FB)
unnamed: C104.2, U10.15 (SS)
unnamed: R37.1, R38.2, R39.2, U12.13 (FB)
unnamed: R40.2, R41.1, R42.2, U13.16 (FB)
unnamed: C114.2, U13.15 (SS)
VDD1V2: C106.1, C109.1, JP1.3 (B), TP8.1, U9.7 (OUT), U9.8 (OUT), U9.9 (OUT), U9.10 (OUT), U9.11 (OUT); also elsewhere on the board
VDD2V5: C115.1, C117.1, R38.1, R39.1, TP4.1, U12.7 (OUT), U12.8 (OUT), U12.9 (OUT), U12.10 (OUT), U12.11 (OUT); also elsewhere on the board
VDD2V5A: C105.1, C108.1, R29.1, R30.1, TP9.1, U8.7 (OUT), U8.8 (OUT), U8.9 (OUT), U8.10 (OUT), U8.11 (OUT); also elsewhere on the board
VDD3V3: C116.1, R40.1, R42.1, TP2.1, U13.1 (OUT), U13.18 (OUT), U13.19 (OUT), U13.20 (OUT); also elsewhere on the board
VDDIO_SERVICE: C107.1, R33.1, R36.1, TP6.1, U10.1 (OUT), U10.18 (OUT), U10.19 (OUT), U10.20 (OUT); also elsewhere on the board

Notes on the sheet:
LDO-based FPGA power generation with cascaded PGOOD/EN sequencing: 2.5 V analog → 1.2 V core → 3.3 V service → 3.3 V user I/O and 2.5 V user I/O.
THP
FPGA Power Regulation & Sequencing
